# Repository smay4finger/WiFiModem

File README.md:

# WiFiModem
A nice looking Hayes compatible modem fully supporting RS232 on the basis of an ESP8266.

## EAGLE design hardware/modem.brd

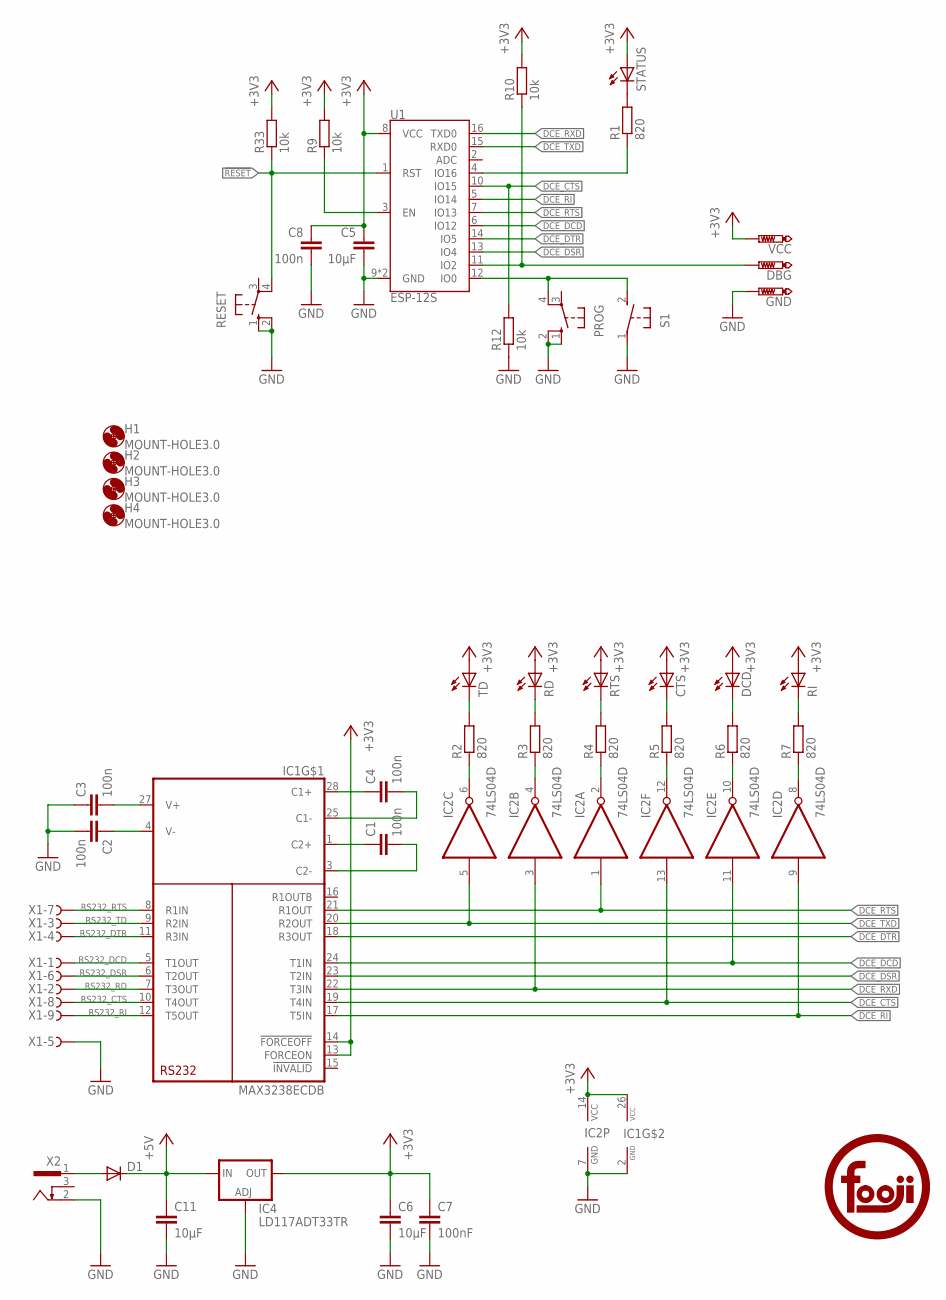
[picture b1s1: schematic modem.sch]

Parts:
C1, C2, C3, C4, C8: 100n; C0805
C5, C6, C11: 10µF; C0805
C7: 100nF; C0805
CTS: LED5MM
D1: DIODE-SMB; SMB
DBG: PTR1PAD1-13; P1-13
DCD: LED5MM
GND: PTR1PAD1-13; P1-13
H1, H2, H3, H4: MOUNT-HOLE3.0; 3,0
IC1: MAX3238ECDB; SSOP28
IC2: 74LS04D; SO14
IC4: LD117ADT33TR; DPACK
PROG: 10-XX; B3F-10XX
R1, R2, R3, R4, R5, R6, R7: 820; R0805
R9, R10, R12, R33: 10k; R0805
RD: LED5MM
RESET: 10-XX; B3F-10XX
RI: LED5MM
RTS: LED5MM
S1: 31-XX; B3F-31XX
STATUS: LED5MM
TD: LED5MM
U1: ESP-12S
U$3: LOGOTOP_NOCIRCLE_TSTOP; LOGO_TOP_NOCIRCLE_TSTOP
VCC: PTR1PAD1-13; P1-13
X1: F09HPS; F09HP
X2: 733980-62

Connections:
!RESET: R33.1, RESET.4 (P1), U1.1 (RST)
+3V3: C5.1, C6.1, C7.1, C8.1, CTS.A, DCD.A, IC1.13 (FORCEON), IC1.14 (!FORCEOFF), IC1.26 (VCC), IC2.14 (VCC), IC4.4 (OUT), R9.2, R10.2, R33.2, RD.A, RI.A, RTS.A, STATUS.A, TD.A, U1.8 (VCC), VCC.TP
+5V: C11.1, D1.C, IC4.3 (IN)
DCE_CTS: IC1.19 (T4IN), IC2.13 (I), R12.2, U1.10 (IO15)
DCE_DCD: IC1.24 (T1IN), IC2.11 (I), U1.6 (IO12)
DCE_DSR: IC1.23 (T2IN), U1.13 (IO4)
DCE_DTR: IC1.18 (R3OUT), U1.14 (IO5)
DCE_RI: IC1.17 (T5IN), IC2.9 (I), U1.5 (IO14)
DCE_RTS: IC1.21 (R1OUT), IC2.1 (I), U1.7 (IO13)
DCE_RXD: IC1.22 (T3IN), IC2.3 (I), U1.16 (TXD0)
DCE_TXD: IC1.20 (R2OUT), IC2.5 (I), U1.15 (RXD0)
DEBUG: DBG.TP, R10.1, U1.11 (IO2)
GND: C2.2, C3.1, C5.2, C6.2, C7.2, C8.2, C11.2, GND.TP, IC1.2 (GND), IC2.7 (GND), IC4.1 (ADJ), PROG.1 (S), PROG.2 (S1), R12.1, RESET.1 (S), RESET.2 (S1), S1.1, U1.9 (GND), U1.P$1 (GND), X1.5 (F), X2.2
unnamed: R1.2, STATUS.K (C)
unnamed: IC2.6 (O), R2.1
unnamed: R9.1, U1.3 (EN)
unnamed: D1.A, X2.1
unnamed: R2.2, TD.K (C)
unnamed: R3.2, RD.K (C)
unnamed: IC2.4 (O), R3.1
unnamed: IC2.2 (O), R4.1
unnamed: IC2.12 (O), R5.1
unnamed: CTS.K (C), R5.2
unnamed: C2.1, IC1.4 (V-)
unnamed: C3.2, IC1.27 (V+)
unnamed: C1.1, IC1.1 (C2+)
unnamed: C1.2, IC1.3 (C2-)
unnamed: C4.2, IC1.25 (C1-)
unnamed: C4.1, IC1.28 (C1+)
unnamed: DCD.K (C), R6.2
unnamed: R7.2, RI.K (C)
unnamed: IC2.8 (O), R7.1
unnamed: IC2.10 (O), R6.1
unnamed: R4.2, RTS.K (C)
unnamed: PROG.4 (P1), S1.2 (S), U1.12 (IO0)
RS232_CTS: IC1.10 (T4OUT), X1.8 (F)
RS232_DCD: IC1.5 (T1OUT), X1.1 (F)
RS232_DSR: IC1.6 (T2OUT), X1.6 (F)
RS232_DTR: IC1.11 (R3IN), X1.4 (F)
RS232_RD: IC1.7 (T3OUT), X1.2 (F)
RS232_RI: IC1.12 (T5OUT), X1.9 (F)
RS232_RTS: IC1.8 (R1IN), X1.7 (F)
RS232_TD: IC1.9 (R2IN), X1.3 (F)
STATUS_A: R1.1, U1.4 (IO16)

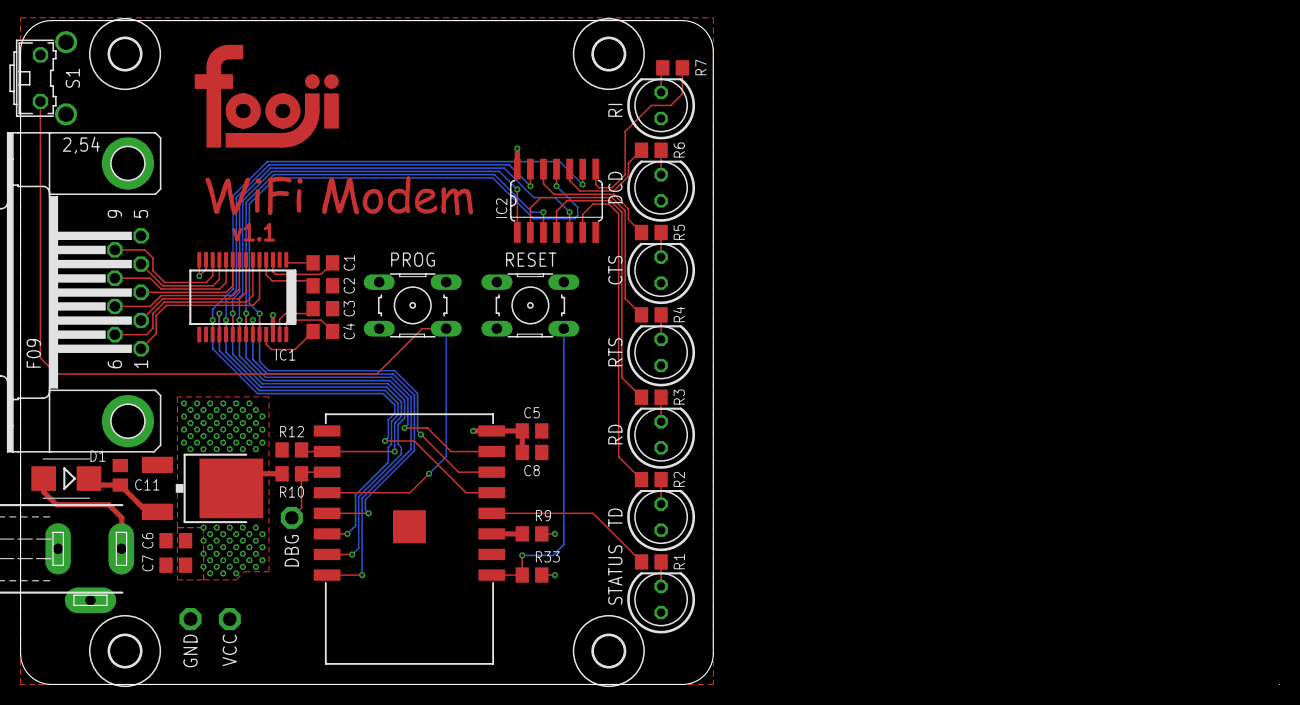
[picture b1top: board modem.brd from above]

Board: 2 copper layers, 122.3 x 64.5 mm, 45 parts (0 on the bottom side), 44 nets.

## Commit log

2020-03-23 first version of PCB
2020-03-23 fixed lots of minor problems of the first prototype
    - mount holes too large (3.2mm instead of 3.0mm)
    - missing keep-out around mount holes
    - resistor collides with screw in mount hole
    - button S1 collides with screw in mount hole
    - C6 and C7 were hard to solder, thermals on around caps
    - LEDs were hard to solder, thermals on VCC layer
2020-03-23 added Makefile for generating gerbers and previews
2020-03-23 added enclosure 3D models
2020-03-24 added photo of hardware v1.0
2020-03-24 updated README.md to include photo of hardware
2021-01-21 added firmware Zimodem from Bo Zimmerman
    https://github.com/bozimmerman/Zimodem/tree/07305c6
2021-01-21 Fix broken up sending of escape sequences
    This is a fix for https://github.com/bozimmerman/Zimodem/issues/31
    Zimodem was sending character received on the serial port to the
    socket one by one. As the TCP stack is configured to send out data as
    soon as possible (setNoDelay), if multiple characters would be
    available to read on the serial port, the first one would always be
    sent to the server immediately. As the IP stack always waits for a
2021-01-21 changed ZIMODEM defines to WIFIMODEM
    This we will do to reflect the huge changes coming. Plan is to remove
    support for ESP32 and also streamline the configuration.
2021-01-21 added README and LICENSE
2021-01-21 changed pinout to actual hardware
2021-01-21 formatted code with Arduino IDE
2021-01-21 added factory reset with button
2021-01-21 rotated image
2021-01-21 removed metadata from image
2021-01-21 added Makefile for firmware building
2021-01-22 use arduino-cli for building
